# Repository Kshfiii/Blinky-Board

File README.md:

# Blinky-Board
A Heart-shaped Blinky Board with 16 LEDs
# Components:
  1x 555 Timer  
  16x LEDs  
  x1 10 μF Capacitor   
  x1 100k Variable Resistor   
  x1 10k Resistor   
  x1 330 ohm resistor    
  x1 Push Button    
  x1 Battery    

# Schemtics 

# PCB

## Bill of Materials
| Component | Quantity | Est. Cost (USD) | Purchase Links | 
| :--- | :---: | :--- | :--- | 
| **LEDs**| 16 | $1.20 | [Link](https://www.aliexpress.com/item/1005008232913389.html?spm=a2g0o.productlist.main.6.3e2f8400vuJPdO&algo_pvid=999f5ad0-b3c6-4a35-b191-18e72b5bafd2&algo_exp_id=999f5ad0-b3c6-4a35-b191-18e72b5bafd2-5&pdp_ext_f=%7B%22order%22%3A%22250%22%2C%22spu_best_type%22%3A%22price%22%2C%22eval%22%3A%221%22%2C%22fromPage%22%3A%22search%22%7D&pdp_npi=6%40dis%21USD%210.73%210.65%21%21%210.73%210.65%21%400b1bf20a17769932437085633e5e97%2112000044317240853%21sea%21PK%210%21ABX%211%210%21n_tag%3A-29910%3Bd%3A12fde4ed%3Bm03_new_user%3A-29895&curPageLogUid=U6wgHChvwvu8&utparam-url=scene%3Asearch%7Cquery_from%3A%7Cx_object_id%3A1005008232913389%7C_p_origin_prod%3A) | 
| **Resistors set**| 1 | $1.30 | [Link](https://www.aliexpress.com/item/1005011772534173.html?spm=a2g0o.productlist.main.2.6ab82805DrF812&algo_pvid=cbf0d139-d756-4cfc-9c08-ab47a8c28a9d&algo_exp_id=cbf0d139-d756-4cfc-9c08-ab47a8c28a9d-1&pdp_ext_f=%7B%22order%22%3A%221777%22%2C%22spu_best_type%22%3A%22price%22%2C%22eval%22%3A%221%22%2C%22fromPage%22%3A%22search%22%7D&pdp_npi=6%40dis%21USD%211.77%211.27%21%21%2112.00%218.61%21%402102f0c917769933012671556eb0c5%2112000056500803485%21sea%21PK%210%21ABX%211%210%21n_tag%3A-29910%3Bd%3A12fde4ed%3Bm03_new_user%3A-29895%3BpisId%3A5000000203713833&curPageLogUid=iRzn684EXIVR&utparam-url=scene%3Asearch%7Cquery_from%3A%7Cx_object_id%3A1005011772534173%7C_p_origin_prod%3A) | 
| **Tactile Switch Set (20pcs)** | 1 | $1.20 |[link](https://www.aliexpress.com/item/1005005845072975.html)| 
| **Capacitors set** | 1 | $1.70 | [Link](https://www.aliexpress.com/item/1005008866352612.html?spm=a2g0o.productlist.main.4.193319fbNWAxXt&aem_p4p_detail=202604231817386751285839399780000685699&algo_pvid=287edbe0-b460-4ba9-90c4-1dd5298f287a&algo_exp_id=287edbe0-b460-4ba9-90c4-1dd5298f287a-3&pdp_ext_f=%7B%22order%22%3A%222129%22%2C%22eval%22%3A%221%22%2C%22fromPage%22%3A%22search%22%7D&pdp_npi=6%40dis%21USD%211.75%211.70%21%21%2111.86%2111.50%21%402102f22c17769934583897878e991f%2112000047038677414%21sea%21PK%210%21ABX%211%210%21n_tag%3A-29910%3Bd%3A12fde4ed%3Bm03_new_user%3A-29895&curPageLogUid=Rp3dWgAbWRdT&utparam-url=scene%3Asearch%7Cquery_from%3A%7Cx_object_id%3A1005008866352612%7C_p_origin_prod%3A&search_p4p_id=202604231817386751285839399780000685699_1) | 
| **PCB** | 1 | $5.50 | [Link](jlcpcb.com) | 
| **Total Build Cost:** |  | **~$10.00** |

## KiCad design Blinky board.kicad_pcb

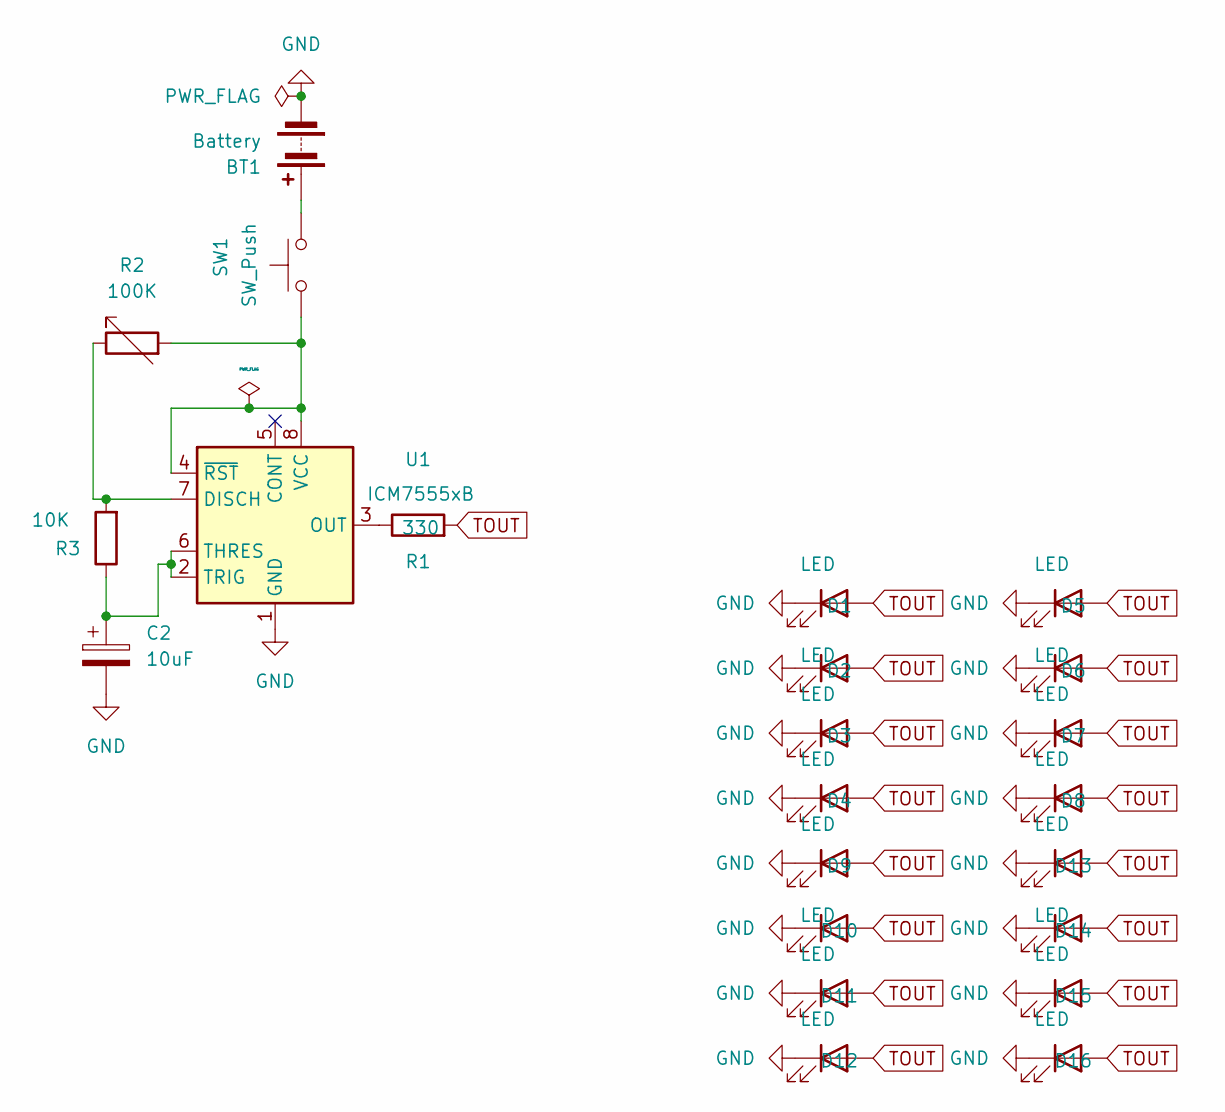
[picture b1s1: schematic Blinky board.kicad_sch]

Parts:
BT1: Battery; TerminalBlock_MaiXu_MX126-5.0-02P_1x02_P5.00mm
C2: 10uF; CP_Radial_D4.0mm_P1.50mm
D1, D2, D3, D4, D5, D6, D7, D8, D9, D10, D11, D12, D13, D14, D15, D16: LED; LED_D3.0mm_FlatTop
R1: 330; R_Axial_DIN0204_L3.6mm_D1.6mm_P5.08mm_Horizontal
R2: 100K; R_Axial_DIN0204_L3.6mm_D1.6mm_P5.08mm_Horizontal
R3: 10K; R_Axial_DIN0204_L3.6mm_D1.6mm_P5.08mm_Horizontal
SW1: SW_Push; SW_PUSH_6mm_H8mm
U1: ICM7555xB; SOIC-8_3.9x4.9mm_P1.27mm

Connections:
GND: BT1.2 (-), C2.2, D1.1 (K), D2.1 (K), D3.1 (K), D4.1 (K), D5.1 (K), D6.1 (K), D7.1 (K), D8.1 (K), D9.1 (K), D10.1 (K), D11.1 (K), D12.1 (K), D13.1 (K), D14.1 (K), D15.1 (K), D16.1 (K), U1.1 (GND)
unnamed: BT1.1 (+), SW1.2
unnamed: R2.1, R3.2, U1.7 (DISCH)
unnamed: R1.1, U1.3 (OUT)
unnamed: C2.1, R3.1, U1.2 (TRIG), U1.6 (THRES)
unnamed: R2.2, SW1.1, U1.4 (~RST), U1.8 (VCC)
TOUT: D1.2 (A), D2.2 (A), D3.2 (A), D4.2 (A), D5.2 (A), D6.2 (A), D7.2 (A), D8.2 (A), D9.2 (A), D10.2 (A), D11.2 (A), D12.2 (A), D13.2 (A), D14.2 (A), D15.2 (A), D16.2 (A), R1.2

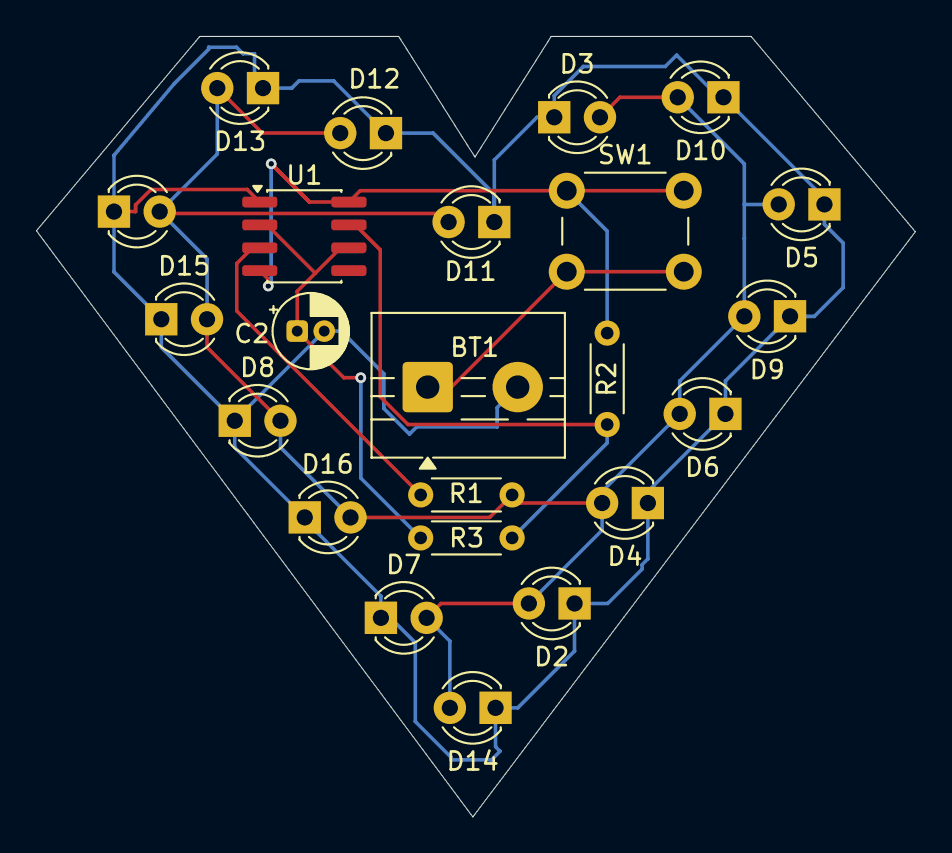
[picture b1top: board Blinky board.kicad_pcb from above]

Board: 2 copper layers, 48.8 x 43.4 mm, 23 parts (0 on the bottom side), 7 nets.

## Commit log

2026-04-24 Add Bill of Materials to README
    Added a Bill of Materials section with components, quantities, estimated costs, and purchase links.
